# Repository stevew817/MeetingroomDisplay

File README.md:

# MeetingroomDisplay
LWM2M-enabled meeting room availability display

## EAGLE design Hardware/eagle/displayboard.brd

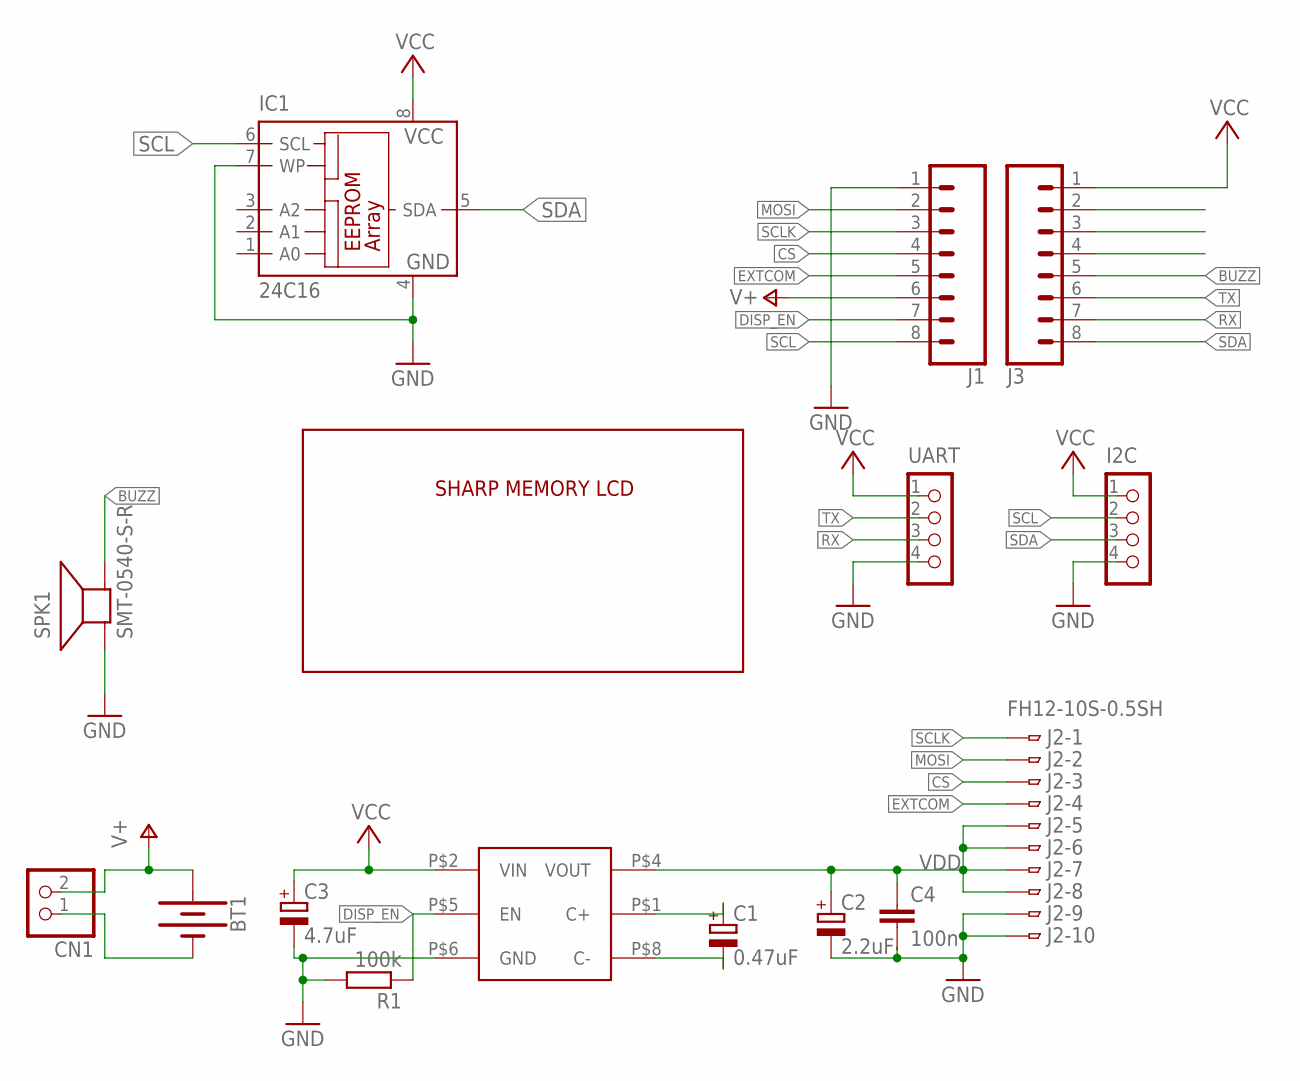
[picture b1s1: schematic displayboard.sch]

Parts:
BT1: BATTERY-18650; BATTERY_18650-HOLDER
C1: 0.47uF; C/6032-28R
C2: 2.2uF; C/6032-28R
C3: 4.7uF; C/6032-28R
C4: 100n; C1206K
CN1: PINHD-1X2; 1X02
I2C: CON_HEADER_1X04; M1X4
IC1: 24C16; SO-08
J1, J3: CONN_08SMD-COMBO-FEMALE; 1X08_SMD_COMBINED
J2: FH12-10S-0.5SH
R1: 100k; R0805
SPK1: SMT-0540-S-R
U$1: S8821; SNT-8A
U$2: MEMORYLCD; LS027B7DH01
UART: CON_HEADER_1X04; M1X4

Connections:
BUZZ: J3.5, SPK1.+ (-)
CS: J1.4, J2.3
DISP_EN: J1.7, R1.1, U$1.P$5 (EN)
EXTCOM: J1.5, J2.4
GND: C2.-, C3.-, C4.2, I2C.4, IC1.4 (GND), IC1.7 (WP), J1.1, J2.9, J2.10, R1.2, SPK1.- (+), U$1.P$6 (GND), UART.4
MOSI: J1.2, J2.2
unnamed: C1.+, U$1.P$1 (C+)
unnamed: C1.-, U$1.P$8 (C-)
unnamed: BT1.GND@1 (-), CN1.1
RX: J3.7, UART.3
SCL: I2C.2, IC1.6 (SCL), J1.8
SCLK: J1.3, J2.1
SDA: I2C.3, IC1.5 (SDA), J3.8
TX: J3.6, UART.2
V+: BT1.PWR@1 (+), CN1.2, J1.6
VCC: C3.+, I2C.1, IC1.8 (VCC), J3.1, U$1.P$2 (VIN), UART.1
VDD: C2.+, C4.1, J2.5, J2.6, J2.7, J2.8, U$1.P$4 (VOUT)

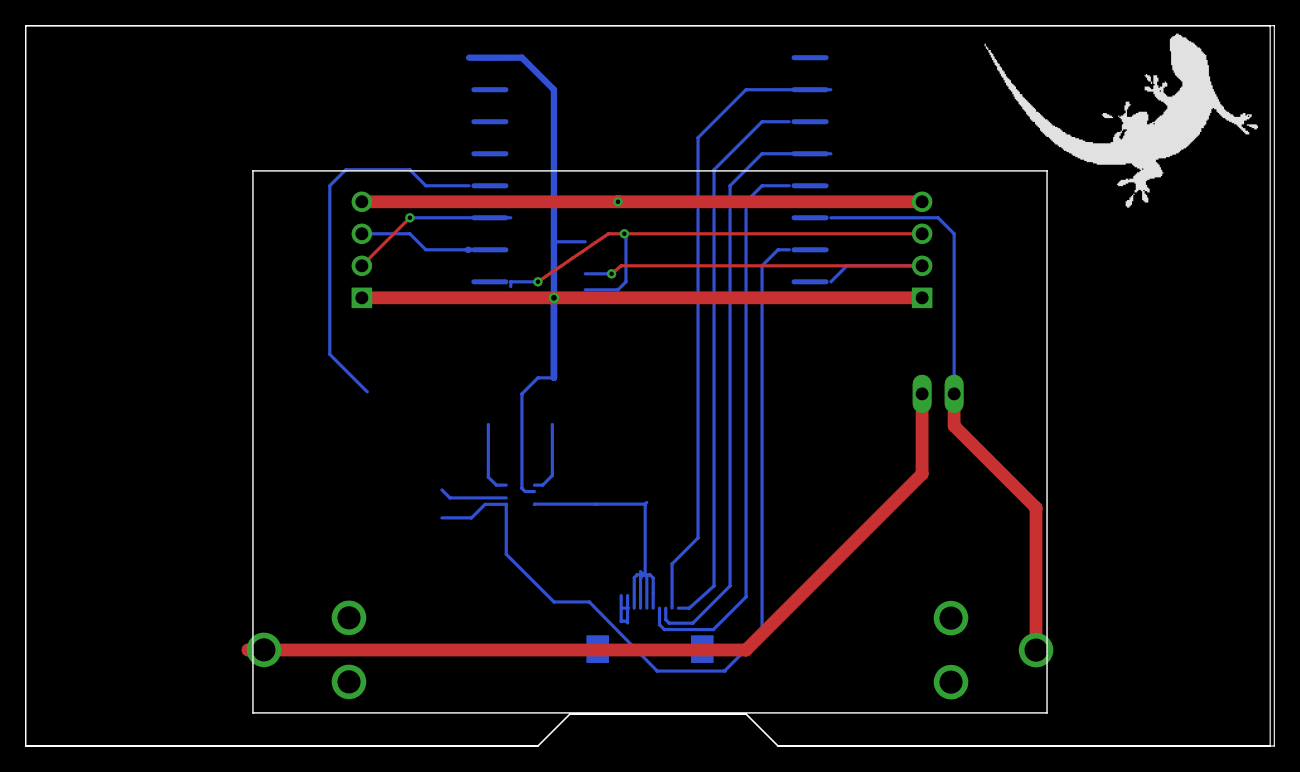
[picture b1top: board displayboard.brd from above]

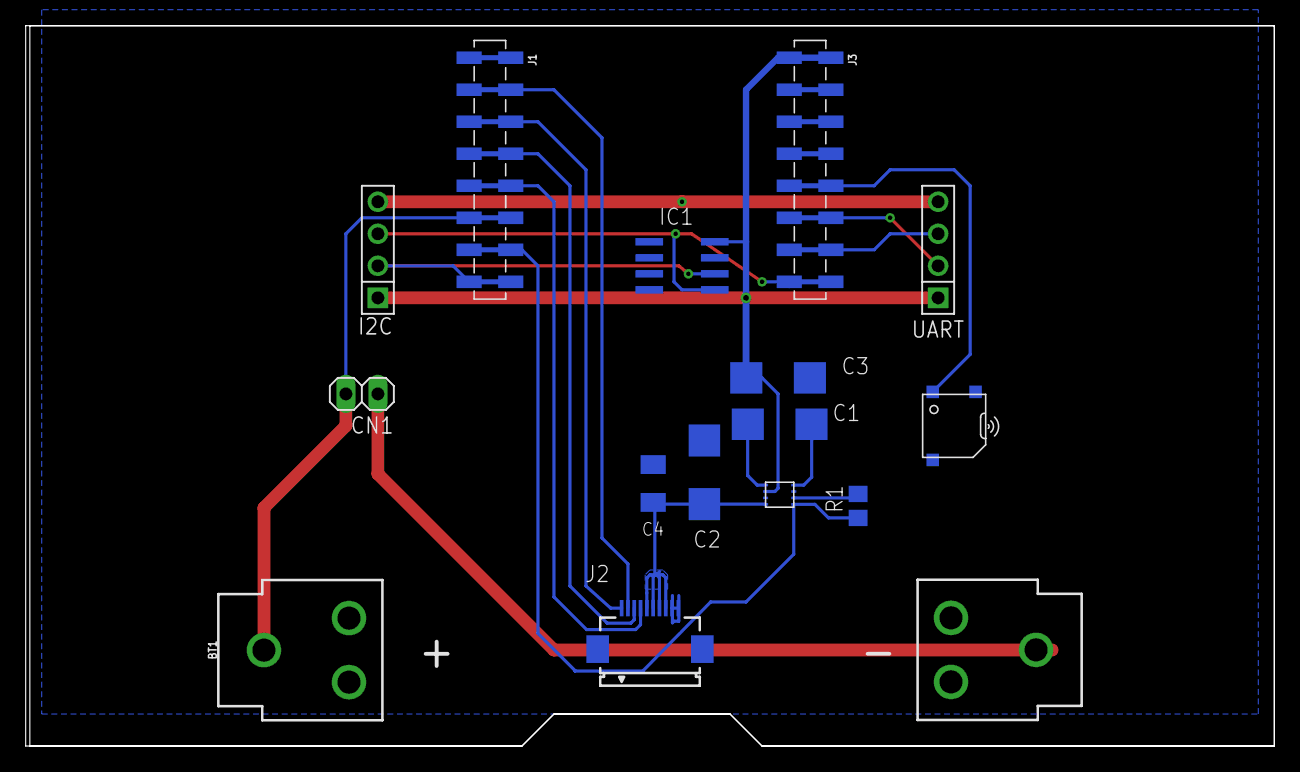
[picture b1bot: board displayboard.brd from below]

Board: 2 copper layers, 99.1 x 57.1 mm, 16 parts (15 on the bottom side), 17 nets.

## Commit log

2017-06-11 [WIP] PCB design for TBSense 2.7" MemLCD backpack
2017-06-11 [WIP] Initial commit of Java daemon
2017-06-11 [WIP] initial commit of firmware project
2017-06-12 Do git submodule correctly
2017-06-16 Update to board design
2017-06-17 Fixup board routing & add EEPROM for identity storage
2017-06-18 Pull in changes from Firmware repo
2017-06-22 Spin a fixed board revision

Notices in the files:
parts and their libraries:
SparkFun-Batteries: Licensing: Creative Commons ShareAlike 4.0 International - https://creativecommons.org/licenses/by-sa/4.0
